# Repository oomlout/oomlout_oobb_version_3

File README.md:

# oomlout_oobb_v3
the oopen building block syste,
## things
[index](things/README.md)

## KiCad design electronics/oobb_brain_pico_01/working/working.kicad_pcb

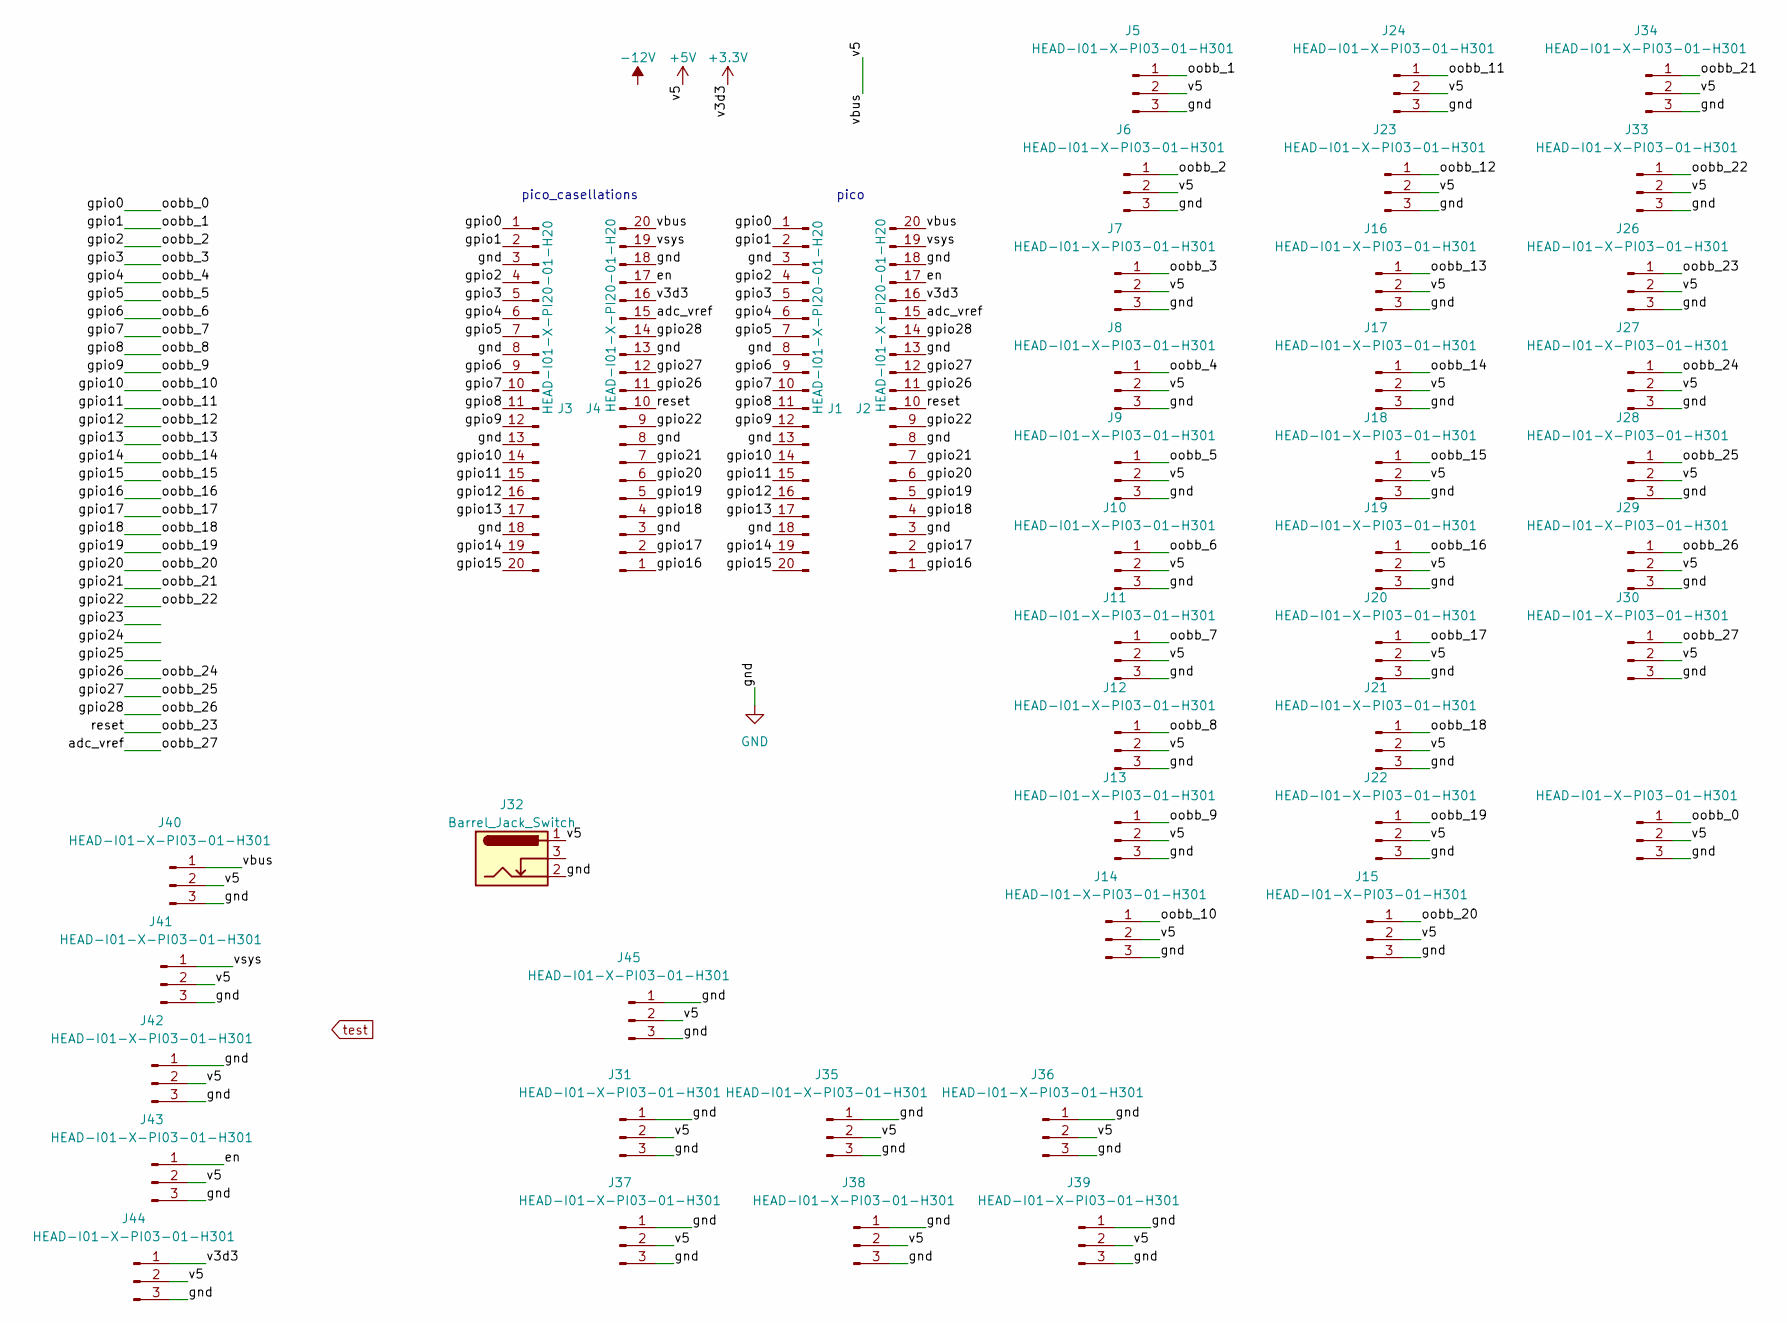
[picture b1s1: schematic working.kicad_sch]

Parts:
J1, J2, J3, J4: HEAD-I01-X-PI20-01-H20
J5, J6, J7, J8, J9, J10, J11, J12, J13, J14, J15, J16, J17, J18, J19, J20, J21, J22, J23, J24, J25, J26, J27, J28, J29, J30, J31, J33, J34, J35, J36, J37, J38, J39, J40, J41, J42, J43, J44, J45: HEAD-I01-X-PI03-01-H301
J32: Barrel_Jack_Switch; BarrelJack_Horizontal

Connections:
+3.3V: J2.16, J4.16, J44.1
+5V: J2.20, J4.20, J5.2, J6.2, J7.2, J8.2, J9.2, J10.2, J11.2, J12.2, J13.2, J14.2, J15.2, J16.2, J17.2, J18.2, J19.2, J20.2, J21.2, J22.2, J23.2, J24.2, J25.2, J26.2, J27.2, J28.2, J29.2, J30.2, J31.2, J32.1, J33.2, J34.2, J35.2, J36.2, J37.2, J38.2, J39.2, J40.1, J40.2, J41.2, J42.2, J43.2, J44.2, J45.2
/adc_vref: J2.15, J4.15, J30.1
/en: J2.17, J4.17, J43.1
/gpio0: J1.1, J3.1, J25.1
/gpio1: J1.2, J3.2, J5.1
/gpio2: J1.4, J3.4, J6.1
/gpio3: J1.5, J3.5, J7.1
/gpio4: J1.6, J3.6, J8.1
/gpio5: J1.7, J3.7, J9.1
/gpio6: J1.9, J3.9, J10.1
/gpio7: J1.10, J3.10, J11.1
/gpio8: J1.11, J3.11, J12.1
/gpio9: J1.12, J3.12, J13.1
/gpio10: J1.14, J3.14, J14.1
/gpio11: J1.15, J3.15, J24.1
/gpio12: J1.16, J3.16, J23.1
/gpio13: J1.17, J3.17, J16.1
/gpio14: J1.19, J3.19, J17.1
/gpio15: J1.20, J3.20, J18.1
/gpio16: J2.1, J4.1, J19.1
/gpio17: J2.2, J4.2, J20.1
/gpio18: J2.4, J4.4, J21.1
/gpio19: J2.5, J4.5, J22.1
/gpio20: J2.6, J4.6, J15.1
/gpio21: J2.7, J4.7, J34.1
/gpio22: J2.9, J4.9, J33.1
/gpio26: J2.11, J4.11, J27.1
/gpio27: J2.12, J4.12, J28.1
/gpio28: J2.14, J4.14, J29.1
/oobb_23: J2.10, J4.10, J26.1
/vsys: J2.19, J4.19, J41.1
GND: J1.3, J1.8, J1.13, J1.18, J2.3, J2.8, J2.13, J2.18, J3.3, J3.8, J3.13, J3.18, J4.3, J4.8, J4.13, J4.18, J5.3, J6.3, J7.3, J8.3, J9.3, J10.3, J11.3, J12.3, J13.3, J14.3, J15.3, J16.3, J17.3, J18.3, J19.3, J20.3, J21.3, J22.3, J23.3, J24.3, J25.3, J26.3, J27.3, J28.3, J29.3, J30.3, J31.1, J31.3, J32.2, J33.3, J34.3, J35.1, J35.3, J36.1, J36.3, J37.1, J37.3, J38.1, J38.3, J39.1, J39.3, J40.3, J41.3, J42.1, J42.3, J43.3, J44.3, J45.1, J45.3

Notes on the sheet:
pico_casellations
pico

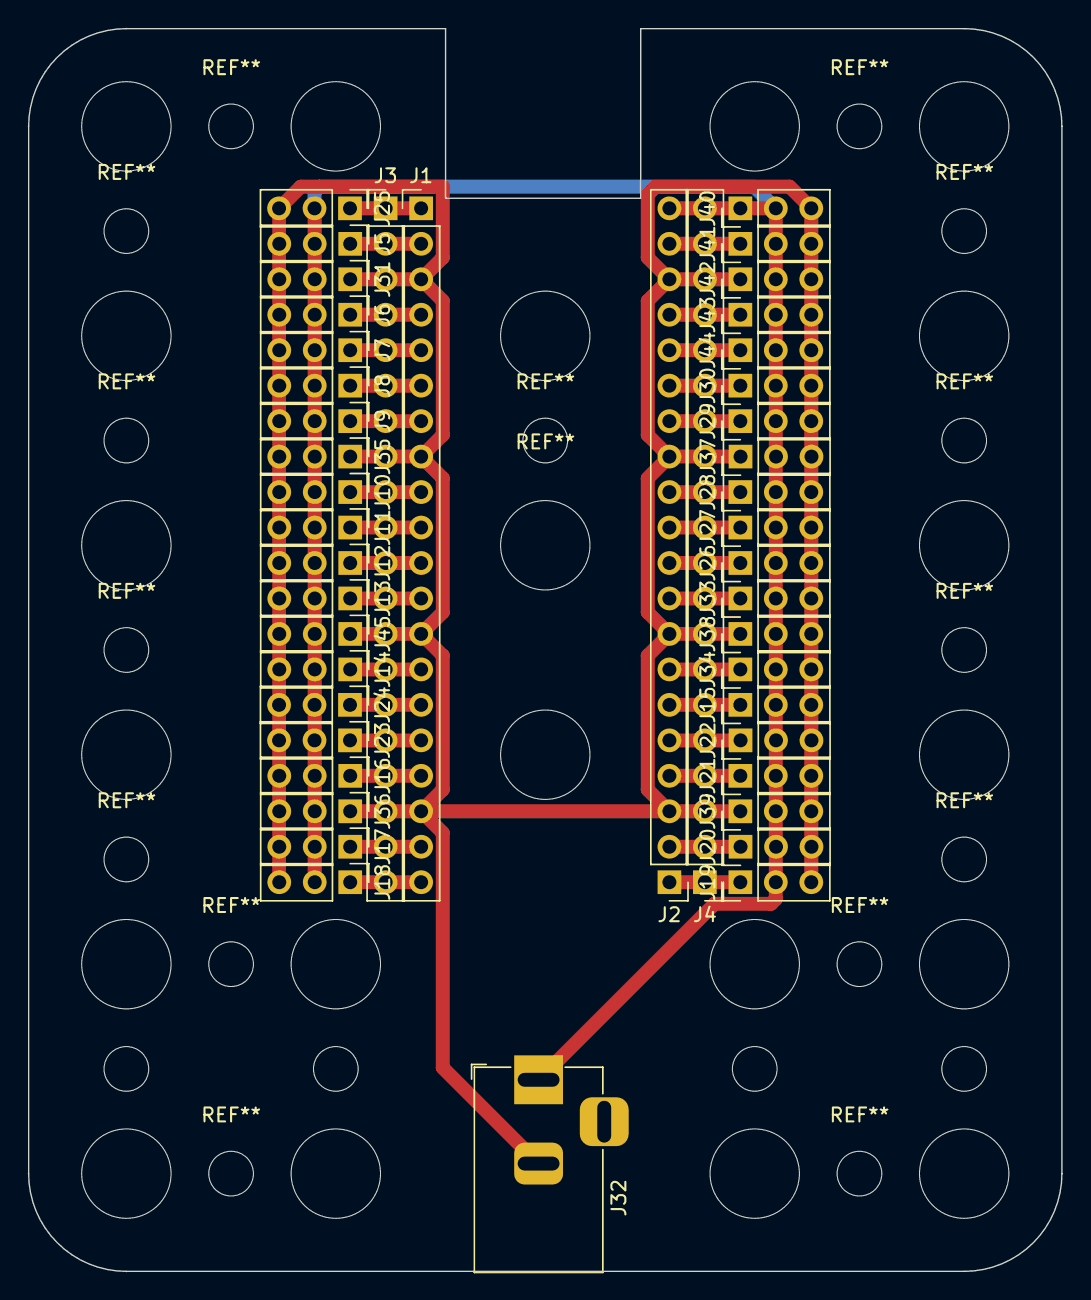
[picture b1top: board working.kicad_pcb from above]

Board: 2 copper layers, 74.0 x 89.0 mm, 45 parts (0 on the bottom side), 33 nets.

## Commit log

2023-03-13 first creation
2023-03-13 al;l changes.
2023-03-13 removed solid python code
2023-03-13 index moved
2023-03-15 full generation
2023-03-17 a few changes
2023-03-17 removing large files
2023-03-17 fixed gitignore
2023-03-17 sorted i think
2023-03-17 a few extra fixes
2023-03-17 readme test
2023-03-17 readme work
2023-03-17 readme messing
2023-03-18 all generated save stp
2023-03-18 stps added only less than 10 mb
2023-03-20 added paper sheet sizes
2023-03-23 workings
2023-04-03 circles and decorations added
2023-04-17 a bit of gearmotor working
2023-05-05 loads!
2023-05-05 a few changes.
2023-05-05 wi work
2023-05-10 bearing plate regen
2023-05-11 redid all non oobb items
2023-05-11 oobe genration
2023-05-29 more workings.
2023-05-29 added readmes
2023-05-31 workings.
2023-06-03 workingsworkings
2023-06-18 working
2023-06-25 decorations added
2023-06-25 decorations
2023-07-10 current state
2023-07-10 rejig of names
2023-07-10 removed old things
2023-07-10 new names
2023-07-10 partial generation
2023-07-13 generated things partial
2023-07-13 fixed working directory some gen
2023-07-13 added larger alphabet bunting
2023-07-13 makling things
2023-07-14 makling things.
2023-07-15 more oobb gen
2023-07-15 a few more
2023-07-16 more plates
2023-07-19 more generation
2023-07-26 a bit of generating new pen holder
2023-07-26 added pen holder
2023-07-30 generated some
2023-07-30 a few
2023-08-02 some generation
2023-08-03 all generated!
2023-08-06 re added decorations
2023-08-26 added basic hub
2023-08-27 full gen i think
2023-08-28 full gen.
2023-08-30 added smd magazines
2023-08-30 smd_magazine_working
2023-08-31 added smd spinner
2023-08-31 mostly smd fussing
2023-09-03 smd and 13_13
2023-09-03 all 13_13
2023-09-13 most things generated
2023-09-15 smd run through
2023-09-15 comitting after 1 generations
2023-10-05 working on actions
2023-10-05 fixed directory name
2023-10-05 trying out
2023-10-05 make it run manually
2023-10-05 bus pirate 5 mounting plate
2023-10-05 readmes
2023-10-13 development pause
